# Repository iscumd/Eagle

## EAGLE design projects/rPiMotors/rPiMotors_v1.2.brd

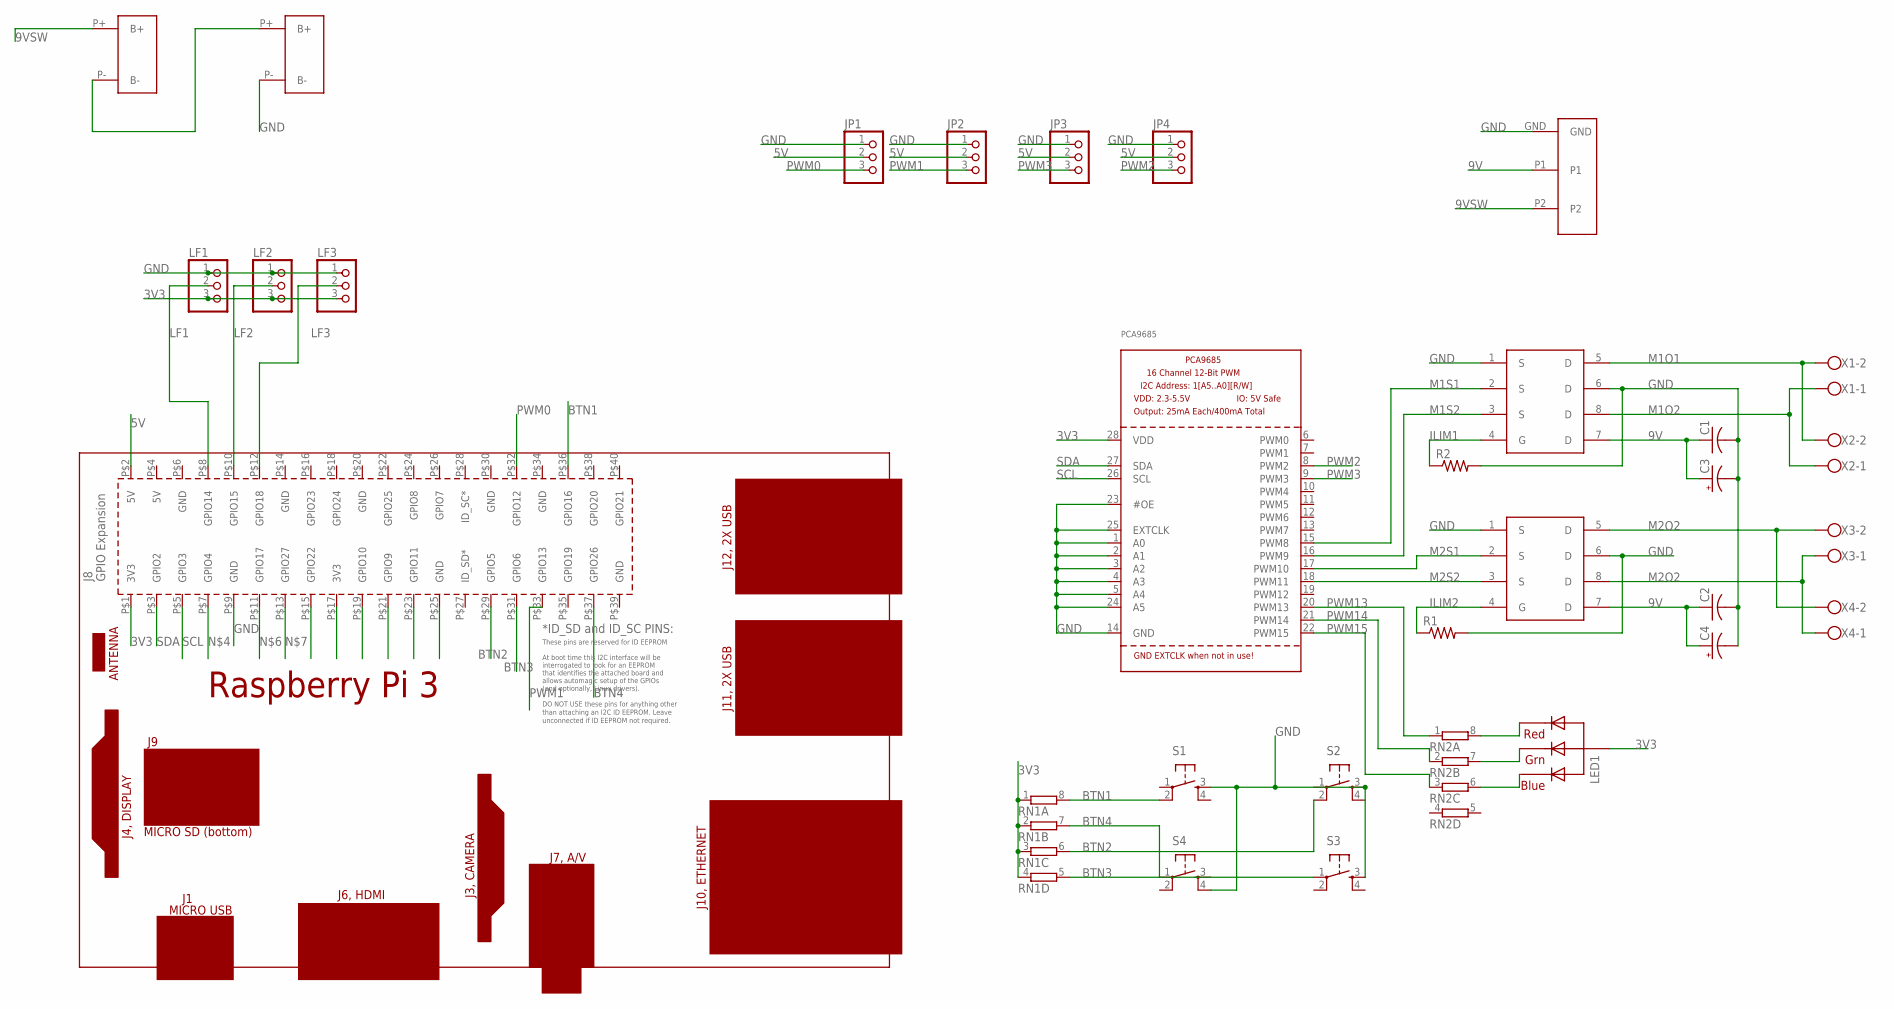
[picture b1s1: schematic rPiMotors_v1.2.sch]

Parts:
C1, C2: C-USC0603; C0603
C3, C4: CPOL-USD; PANASONIC_D
JP1, JP2, JP3, JP4: PINHD-1X3; 1X03
LED1: RGBLED_CA; 5MMRGB
LF1, LF2, LF3: PINHD-1X3; 1X03
PCA9685: PCA9685; TSSOP28
PCB1: RPI3
R1, R2: R-US_R0603; R0603
RN1, RN2: 4R-N0603-ARV; 0603-ARV
S1, S2, S3, S4: TAC_SWITCHPTH; TACTILE-PTH
U$1, U$2: NDS8434; SO08
U$3: ROCKER
U$4, U$5: BATTERY
X1, X2, X3, X4: SCREWCONNECTOR; 2PIN-SCREW-TERMINAL

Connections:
3V3: LED1.2 (VCC), LF1.3, LF2.3, LF3.3, PCA9685.28 (VDD), PCB1.P$1 (3V3), RN1.1, RN1.2 (1), RN1.3 (1), RN1.4 (1)
5V: JP1.2, JP2.2, JP3.2, JP4.2, PCB1.P$2 (5V)
9V: C1.1, C2.1, C3.+, C4.+, U$1.7 (D), U$2.7 (D), U$3.P1
9VSW: U$3.P2, U$4.P+ (B+)
BTN1: PCB1.P$36 (GPIO16), RN1.8 (2), S1.2
BTN2: PCB1.P$29 (GPIO5), RN1.6 (2), S2.2
BTN3: PCB1.P$31 (GPIO6), RN1.5 (2), S3.1
BTN4: PCB1.P$37 (GPIO26), RN1.7 (2), S4.1
GND: C1.2, C2.2, C3.-, C4.-, JP1.1, JP2.1, JP3.1, JP4.1, LF1.1, LF2.1, LF3.1, PCA9685.1 (A0), PCA9685.2 (A1), PCA9685.3 (A2), PCA9685.4 (A3), PCA9685.5 (A4), PCA9685.14 (GND), PCA9685.23 (#OE), PCA9685.24 (A5), PCA9685.25 (EXTCLK), PCB1.P$9 (GND), R1.2, R2.2, S1.3, S2.3, S3.3, S4.4, U$1.1 (S), U$1.6 (D), U$2.1 (S), U$2.6 (D), U$3.GND, U$5.P- (B-)
ILIM1: R2.1, U$1.4 (G)
ILIM2: R1.1, U$2.4 (G)
LF1: LF1.2, PCB1.P$8 (GPIO14)
LF2: LF2.2, PCB1.P$10 (GPIO15)
LF3: LF3.2, PCB1.P$12 (GPIO18)
M1O1: U$1.5 (D), X1.2, X2.2
M1O2: U$1.8 (D), X1.1, X2.1
M1S1: PCA9685.15 (PWM8), U$1.2 (S)
M1S2: PCA9685.16 (PWM9), U$1.3 (S)
M2O2: U$2.5 (D), U$2.8 (D), X3.1, X3.2, X4.1, X4.2
M2S1: PCA9685.17 (PWM10), U$2.2 (S)
M2S2: PCA9685.18 (PWM11), U$2.3 (S)
unnamed: LED1.3 (GREEN), RN2.7 (2)
unnamed: U$4.P- (B-), U$5.P+ (B+)
PWM0: JP1.3, PCB1.P$32 (GPIO12)
PWM1: JP2.3, PCB1.P$33 (GPIO13)
PWM2: JP4.3, PCA9685.8 (PWM2)
PWM3: JP3.3, PCA9685.9 (PWM3)
PWM13: PCA9685.20 (PWM13), RN2.1
PWM14: PCA9685.21 (PWM14), RN2.2 (1)
PWM15: PCA9685.22 (PWM15), RN2.3 (1)
SCL: PCA9685.26 (SCL), PCB1.P$5 (GPIO3)
SDA: PCA9685.27 (SDA), PCB1.P$3 (GPIO2)

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
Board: 2 copper layers, 31 parts (0 on the bottom side), 34 nets, no tracks yet.

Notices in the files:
parts and their libraries:
SparkFun-Retired: Licensing:Creative Commons ShareAlike 4.0 International - https://creativecommons.org/licenses/by-sa/4.0
